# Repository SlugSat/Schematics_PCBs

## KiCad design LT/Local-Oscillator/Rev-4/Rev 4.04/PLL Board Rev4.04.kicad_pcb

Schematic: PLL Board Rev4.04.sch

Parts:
C1, C13, C14: C; C_0805_2012Metric_Pad1.15x1.40mm_HandSolder
C2, C5, C6, C9, C10, C17, C18, C21, C22, C29: 100nF; C_0805_2012Metric_Pad1.15x1.40mm_HandSolder
C3, C7, C11, C25, C26, C28: 100pF; C_0805_2012Metric_Pad1.15x1.40mm_HandSolder
C4, C8: 1000pF; C_0805_2012Metric_Pad1.15x1.40mm_HandSolder
C12: 12nF; C_0805_2012Metric_Pad1.15x1.40mm_HandSolder
C15: 22pF; C_0805_2012Metric_Pad1.15x1.40mm_HandSolder
C16: 47pF; C_0805_2012Metric_Pad1.15x1.40mm_HandSolder
C19: SGC35060; C_Trimmer_Murata_TZB4-B
C20: 10pF; C_0805_2012Metric_Pad1.15x1.40mm_HandSolder
C23: 80nF; C_0805_2012Metric_Pad1.15x1.40mm_HandSolder
C24: 220nF; C_0805_2012Metric_Pad1.15x1.40mm_HandSolder
D1, D5: DIODE; D_DO-41_SOD81_P10.16mm_Horizontal
D3, D4: ???; D_SC-80_HandSoldering
FL1: Conn_Coaxial; SMA_Molex_73251-1153_EdgeMount_Horizontal
FoLD1: Conn_Coaxial; SMA_Molex_73251-1153_EdgeMount_Horizontal
J1, J5, J7, J8, J13, J14, J15, J16, J17, J20: Conn_01x02_Male; PinHeader_1x02_P2.54mm_Vertical
J2, J3, J18: Conn_Coaxial; SMA_Molex_73251-1153_EdgeMount_Horizontal
J4: Conn_01x04_Male; PinHeader_1x04_P2.54mm_Vertical
L1: 680nH; L_0805_2012Metric_Pad1.15x1.40mm_HandSolder
OSC_OUT1: Conn_Coaxial; SMA_Molex_73251-1153_EdgeMount_Horizontal
Q1, Q2: 2N5486 JFET; TO-251-3_Vertical
R1, R3, R4: 18; R_0805_2012Metric_Pad1.15x1.40mm_HandSolder
R2: 10k; R_0805_2012Metric_Pad1.15x1.40mm_HandSolder
R5: R; R_0805_2012Metric_Pad1.15x1.40mm_HandSolder
R6, R9, R11, R12: 1k; R_0805_2012Metric_Pad1.15x1.40mm_HandSolder
R7: 62k; R_0805_2012Metric_Pad1.15x1.40mm_HandSolder
R8: 1 Ohm; R_0805_2012Metric_Pad1.15x1.40mm_HandSolder
R10: 100k; R_0805_2012Metric_Pad1.15x1.40mm_HandSolder
R13, R14: 0; R_0805_2012Metric_Pad1.15x1.40mm_HandSolder
Test_CP1: Conn_Coaxial; SMA_Molex_73251-1153_EdgeMount_Horizontal
U1: LMX231X
U2: L7808; TO-220F-3_Vertical

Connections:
8V: C18.2, C22.2, C25.2, C26.2, Q1.1 (D), Q2.1 (D), U2.3 (OUT)
CE: C5.2, R2.2, U1.15 (CE)
CPo: J20.1, U1.2 (CPo)
Clock: J4.3, U1.10 (Clock)
Data: J4.2, U1.12 (Data)
FL: FL1.1 (In), U1.19 (FL)
F_IN: C4.2, U1.4 (F_IN)
FoLD: FoLD1.1 (In), U1.9 (FoLD)
GND: C1.1, C2.1, C3.1, C5.1, C6.1, C7.1, C9.1, C10.1, C11.1, C12.1, C13.2, C14.2, C16.1, C18.1, C19.2, C21.2, C22.1, C23.2, C24.2, C25.1, C26.1, C28.1, C29.1, D4.2 (A), FL1.2 (Ext), FoLD1.2 (Ext), J1.2, J2.2 (Ext), J3.2 (Ext), J4.4, J8.2, J17.1, J18.2 (Ext), L1.2, OSC_OUT1.2 (Ext), R9.2, R10.2, R11.2, Test_CP1.2 (Ext), U1.1 (NC), U1.3 (GND), U1.7 (NC), U1.11 (NC), U1.14 (GND), U1.17 (NC), U2.2 (GND)
LE: J4.1, U1.13 (LE)
unnamed: C4.1, J5.1, J7.2
unnamed: C8.1, J3.1 (In)
unnamed: C9.2, U1.5 (F_INB)
unnamed: C12.2, J13.1, R6.2, R7.2
unnamed: C13.1, J14.1, J15.1, R5.2
unnamed: C14.1, R5.1
unnamed: C15.1, C16.2, C20.1, Q1.2 (S), R9.1
unnamed: C15.2, C19.1, D3.2 (A), L1.1, Q1.3 (G)
unnamed: C17.1, J7.1, Q2.2 (S), R11.1
unnamed: C17.2, J18.1 (In)
unnamed: C20.2, R8.2
unnamed: C21.1, D5.2 (A), U2.1 (IN)
unnamed: C23.1, R7.1
unnamed: C24.1, J16.1, R6.1
unnamed: C28.2, C29.2, J8.1, R12.2
unnamed: D1.1 (K), J1.1
unnamed: D3.1 (K), D4.1 (K), R12.1, R13.2, R14.2
unnamed: D5.1 (K), J17.2
unnamed: J2.1 (In), J5.2
unnamed: J13.2, J14.2, J20.2, Test_CP1.1 (In)
unnamed: J15.2, R13.1
unnamed: J16.2, R14.1
unnamed: Q2.3 (G), R8.1, R10.1
OSC_IN: C8.2, U1.6 (OSC_IN)
OSC_OUT: OSC_OUT1.1 (In), U1.8 (OSC_OUT)
PLL_Power: C1.2, D1.2 (A), R1.1, R2.1, R3.1, R4.1
V_uC: C2.2, C3.2, R1.2, U1.16 (V_uC)
Vcc: C6.2, C7.2, R3.2, U1.18 (Vcc)
Vp: C10.2, C11.2, R4.2, U1.20 (Vp)

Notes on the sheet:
Reference Oscillator (i)
VCO Small Signal Feedback (i)
Charge Pumps to VCO (o)
VCO Tuning Voltage (i)
VCO Output
Charge Pump Filters
VCO Power
PLL Power
PLL Board
1/3/20
Test Charge Pumps (i)
VCO Test Oscillator (i)
Mircowire Interface
Loop Filter Output
Rev4.04: The Variable Capacitor was changed to the specific trimmer SGC35060

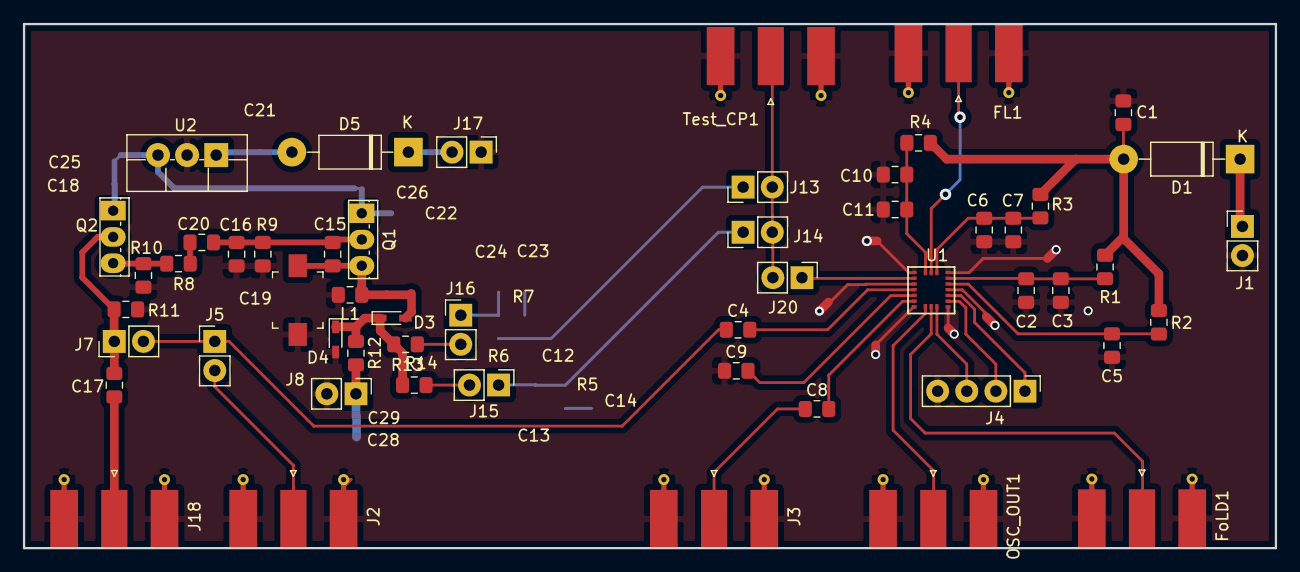
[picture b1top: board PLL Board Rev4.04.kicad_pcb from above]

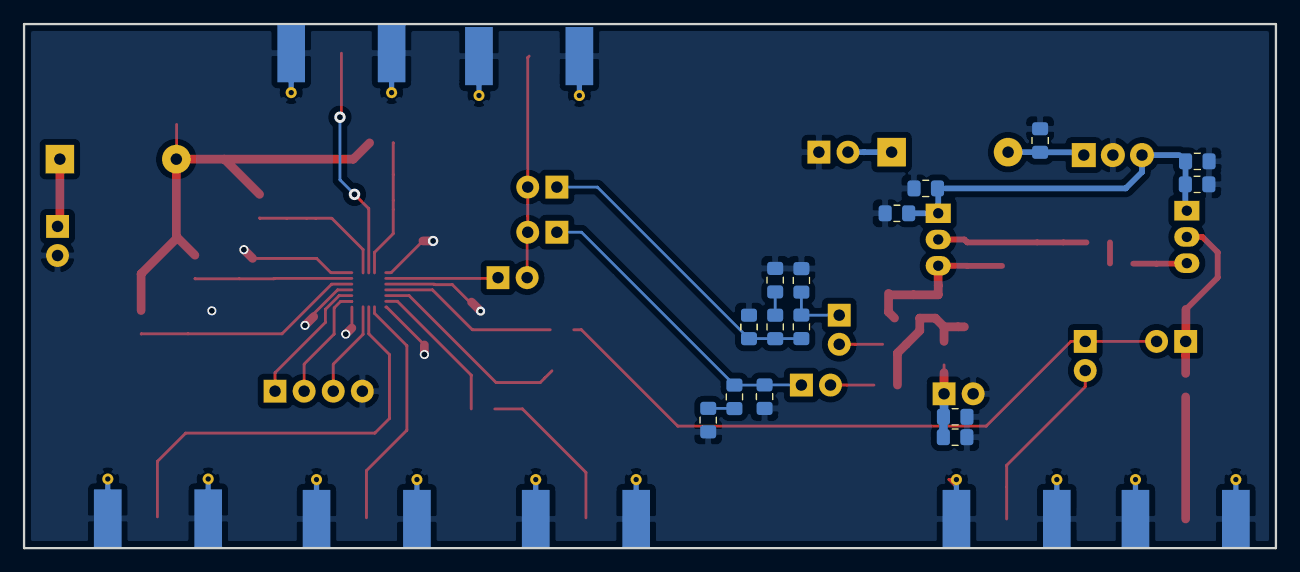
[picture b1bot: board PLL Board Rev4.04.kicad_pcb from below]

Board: 2 copper layers, 109.2 x 45.7 mm, 69 parts (15 on the bottom side), 39 nets.

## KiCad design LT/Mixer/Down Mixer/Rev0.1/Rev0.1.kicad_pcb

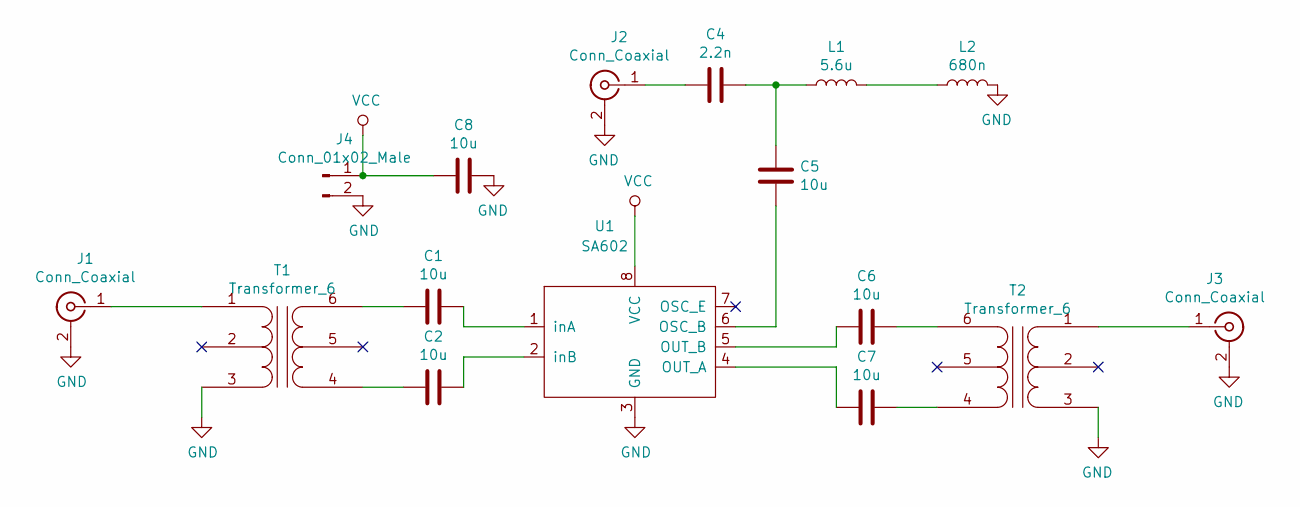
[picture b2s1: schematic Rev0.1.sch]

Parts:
C1, C2, C5, C6, C7, C8: 10u; C_0805_2012Metric_Pad1.15x1.40mm_HandSolder
C4: 2.2n; C_0805_2012Metric_Pad1.15x1.40mm_HandSolder
J1, J2, J3: Conn_Coaxial; SMA_Amphenol_132289_EdgeMount
J4: Conn_01x02_Male; PinHeader_1x02_P2.54mm_Vertical
L1: 5.6u; C_0805_2012Metric_Pad1.15x1.40mm_HandSolder
L2: 680n; C_0805_2012Metric_Pad1.15x1.40mm_HandSolder
T1, T2: Transformer_6; PWB1040L
U1: SA602; SO-8_3.9x4.9mm_P1.27mm

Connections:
GND: C8.2, J1.2 (Ext), J2.2 (Ext), J3.2 (Ext), J4.2, L2.2, T1.3 (AB), T2.3 (AB), U1.3 (GND)
unnamed: C1.1, U1.1 (inA)
unnamed: C1.2, T1.6 (SB)
unnamed: C2.1, U1.2 (inB)
unnamed: C2.2, T1.4 (SA)
unnamed: C4.1, J2.1 (In)
unnamed: C4.2, C5.1, L1.1
unnamed: C5.2, U1.6 (OSC_B)
unnamed: C6.1, U1.5 (OUT_B)
unnamed: C6.2, T2.6 (SB)
unnamed: C7.1, U1.4 (OUT_A)
unnamed: C7.2, T2.4 (SA)
unnamed: J1.1 (In), T1.1 (AA)
unnamed: J3.1 (In), T2.1 (AA)
unnamed: L1.2, L2.1
VCC: C8.1, J4.1, U1.8 (VCC)

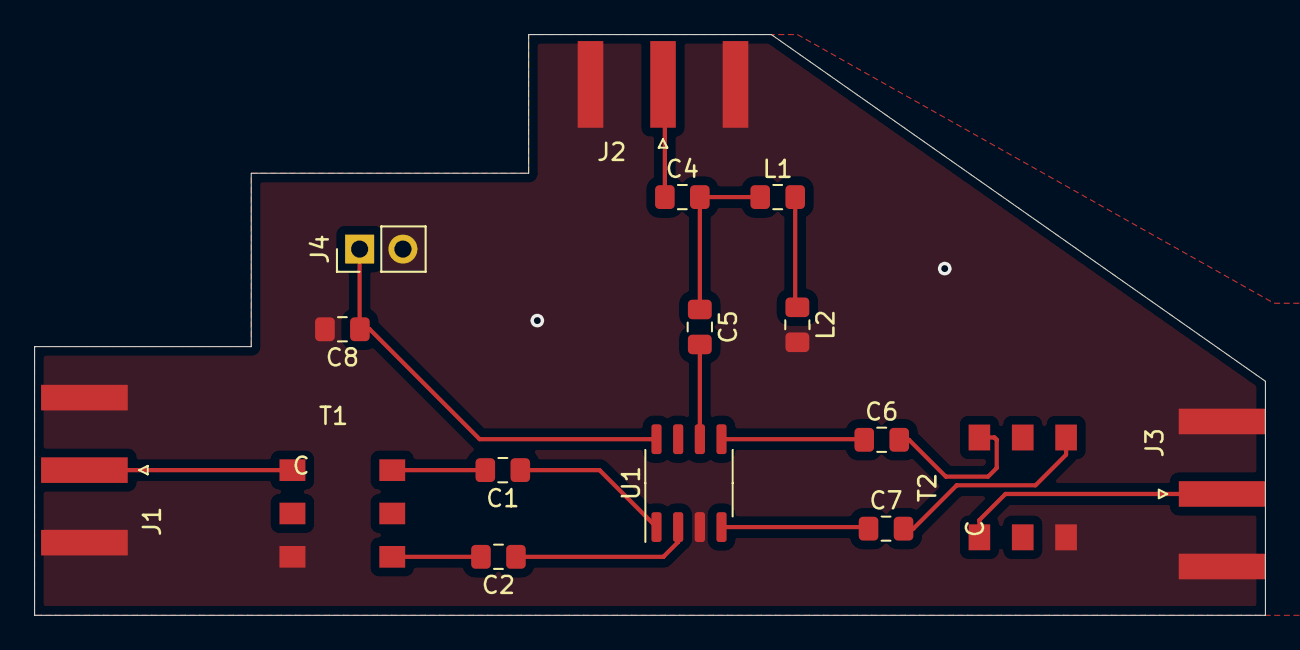
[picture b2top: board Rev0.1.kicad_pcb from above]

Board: 2 copper layers, 72.1 x 34.0 mm, 16 parts (0 on the bottom side), 16 nets.
